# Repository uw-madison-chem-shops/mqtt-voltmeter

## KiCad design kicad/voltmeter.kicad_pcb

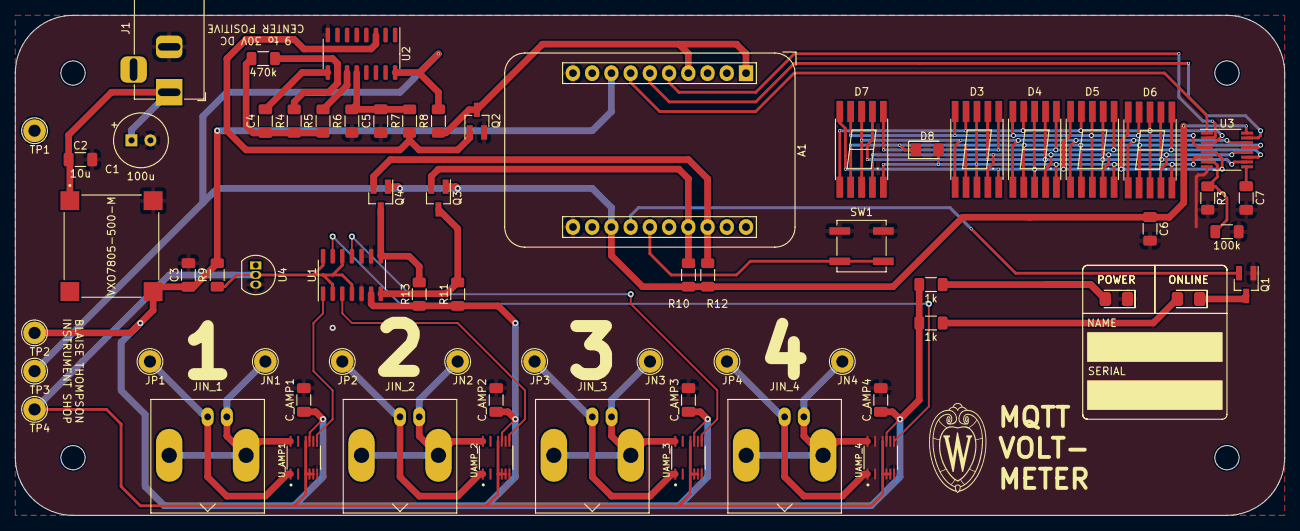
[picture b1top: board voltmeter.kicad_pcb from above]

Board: 2 copper layers, 167.6 x 66.0 mm, 68 parts (0 on the bottom side), 47 nets.

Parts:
A1: Adafruit_HUZZAH_ESP8266_breakout
C1: 100u; CP_Radial_Tantal_D7.0mm_P2.50mm
C2: 10u; C_1206_3216Metric_Pad1.33x1.80mm_HandSolder
C3: 22u; C_1206_3216Metric_Pad1.33x1.80mm_HandSolder
C4, C5: 1u; C_1206_3216Metric_Pad1.33x1.80mm_HandSolder
C6: 100n; C_1206_3216Metric_Pad1.33x1.80mm_HandSolder
C7: 20p; C_1206_3216Metric_Pad1.33x1.80mm_HandSolder
C_AMP1, C_AMP2, C_AMP3, C_AMP4: 100n; C_1206_3216Metric_Pad1.33x1.80mm_HandSolder
D1, D1#2, D2, D2#2, D8: LED; LED_1206_3216Metric_Pad1.42x1.75mm_HandSolder
D3, D4, D5, D6, D7: ACSC02-41SURKWA-F01
J1: Barrel_Jack; BarrelJack_Horizontal
JIN_1, JIN_2, JIN_3, JIN_4: IN-COAX; BNC_Amphenol_B6252HB-NPP3G-50_Horizontal
JN1, JN2, JN3, JN4: IN-; TestPoint_Loop_D2.60mm_Drill1.6mm_Beaded
JP1, JP2, JP3, JP4: IN+; TestPoint_Loop_D2.60mm_Drill1.6mm_Beaded
PS1: VXO7805-500-M; CONV_VXO7805-500-M
Q1, Q2, Q3, Q4: 2N7000; SOT-23_Handsoldering
R1, R2: 1k; R_1206_3216Metric_Pad1.30x1.75mm_HandSolder
R3, R3#2: 100k; R_1206_3216Metric_Pad1.30x1.75mm_HandSolder
R4, R4#2: 470k; R_1206_3216Metric_Pad1.30x1.75mm_HandSolder
R5, R6: 1M; R_1206_3216Metric_Pad1.30x1.75mm_HandSolder
R7, R8: 4.7k; R_1206_3216Metric_Pad1.30x1.75mm_HandSolder
R9: 470; R_1206_3216Metric_Pad1.30x1.75mm_HandSolder
R10, R11, R12, R13: 4K7; R_1206_3216Metric_Pad1.30x1.75mm_HandSolder
SW1: SW_Push; SW_SPST_B3SL-1022P
TP1, TP2, TP3, TP4: TestPoint; TestPoint_Loop_D2.60mm_Drill1.6mm_Beaded
U1: MCP3428; SOIC-14_3.9x8.7mm_P1.27mm
U2: CD4060BM96; SOIC-16_3.9x9.9mm_P1.27mm
U3: MAX6951; QSOP-16_3.9x4.9mm_P0.635mm
U4: LM285Z-2.5; TO-92_Inline
UAMP_2, UAMP_3, UAMP_4: LT1997HMS-3#PBF; SOP50P490X110-16N
U_AMP1: LT1997HMS-3#PBF; SOP50P490X110-16N

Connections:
+2V5: R9.2, TP4.1, U1.2 (CH1-), U1.4 (CH2-), U1.12 (CH3-), U1.14 (CH4-), U4.2 (K), UAMP_2.5 (+INC), UAMP_2.6 (REF1), UAMP_2.7 (REF2), UAMP_2.12 (-INC), UAMP_3.5 (+INC), UAMP_3.6 (REF1), UAMP_3.7 (REF2), UAMP_3.12 (-INC), UAMP_4.5 (+INC), UAMP_4.6 (REF1), UAMP_4.7 (REF2), UAMP_4.12 (-INC), U_AMP1.5 (+INC), U_AMP1.6 (REF1), U_AMP1.7 (REF2), U_AMP1.12 (-INC)
+3V3: A1.13 (3V), C6.1, Q3.1 (G), Q4.1 (G), R8.1, R10.1, R12.1, TP3.1, U2.16 (VDD), U3.16 (V+)
+5V: A1.8 (V+), C3.1, C_AMP1.1, C_AMP2.1, C_AMP3.1, C_AMP4.1, PS1.3 (+VO), R1.1, R2.1, R9.1, R11.1, R13.1, TP2.1, U1.6 (VDD), UAMP_2.11 (V+), UAMP_3.11 (V+), UAMP_4.11 (V+), U_AMP1.11 (V+)
/difference-amplifier1/V_OUT: U1.1 (CH1+), U_AMP1.9 (OUT)
/difference-amplifier2/V_OUT: U1.3 (CH2+), UAMP_2.9 (OUT)
/difference-amplifier3/V_OUT: U1.11 (CH3+), UAMP_3.9 (OUT)
/difference-amplifier4/V_OUT: U1.13 (CH4+), UAMP_4.9 (OUT)
/display/SEG0: D3.3 (C.K.), D3.8 (C.K.), D4.5 (DP), D5.5 (DP), D6.5 (DP), D7.5 (DP), D8.2 (A), U3.6 (DIG0/SEG0)
/display/SEG1: D3.5 (DP), D4.3 (C.K.), D4.8 (C.K.), D5.10 (g), D6.10 (g), D7.10 (g), U3.5 (DIG1/SEG1)
/display/SEG2: D3.10 (g), D4.10 (g), D5.3 (C.K.), D5.8 (C.K.), D6.9 (f), D7.9 (f), U3.4 (DIG2/SEG2)
/display/SEG3: D3.9 (f), D4.9 (f), D5.9 (f), D6.3 (C.K.), D6.8 (C.K.), D7.1 (e), U3.3 (DIG3/SEG3)
/display/SEG4: D3.1 (e), D4.1 (e), D5.1 (e), D6.1 (e), D7.3 (C.K.), D7.8 (C.K.), U3.14 (DIG4/SEG4)
/display/SEG5: D3.2 (d), D4.2 (d), D5.2 (d), D6.2 (d), D7.2 (d), D8.1 (K), U3.13 (DIG5/SEG5)
/display/SEG6: D3.4 (c), D4.4 (c), D5.4 (c), D6.4 (c), D7.4 (c), U3.12 (DIG6/SEG6)
/display/SEG7: D3.6 (b), D4.6 (b), D5.6 (b), D6.6 (b), D7.6 (b), U3.11 (DIG7/SEG7)
/display/SEG8: D3.7 (a), D4.7 (a), D5.7 (a), D6.7 (a), D7.7 (a), U3.10 (SEG8)
/i2c-levelshift/SCL_HV: Q4.3 (D), R13.2, U1.8 (SCL)
/i2c-levelshift/SDA_HV: Q3.3 (D), R11.2, U1.7 (SDA)
DISPLAY_CS: A1.6 (12), U3.15 (~CS)
GND: A1.10 (GND), A1.11 (GND), C1.2, C2.2, C3.2, C5.2, C6.2, C7.2, C_AMP1.2, C_AMP2.2, C_AMP3.2, C_AMP4.2, D1.1 (K), D1#2.1 (K), J1.2, PS1.2 (GND), Q1.1 (S), Q2.2 (S), R3.2, R3#2.2, R6.2, SW1.1, TP1.1, U1.5 (VSS), U1.9 (Adr0), U1.10 (Adr1), U2.8 (GND), U3.8 (GND), U4.3 (A), UAMP_2.8 (V-), UAMP_3.8 (V-), UAMP_4.8 (V-), U_AMP1.8 (V-)
MOSI: A1.7 (13), U3.1 (DIN)
unnamed: A1.15 (2), SW1.2
unnamed: A1.14 (15), Q1.2 (G)
unnamed: C4.2, R4.1, R4#2.1, R5.1
unnamed: D1.2 (A), D1#2.2 (A), R1.2
unnamed: D2.2 (A), D2#2.2 (A), R2.2
unnamed: D2.1 (K), D2#2.1 (K), Q1.3 (D)
unnamed: JIN_1.2 (Ext), JN1.1, U_AMP1.16 (-INA)
unnamed: JIN_1.1 (In), JP1.1, U_AMP1.1 (+INA)
unnamed: JIN_2.2 (Ext), JN2.1, UAMP_2.16 (-INA)
unnamed: JIN_2.1 (In), JP2.1, UAMP_2.1 (+INA)
unnamed: JIN_3.2 (Ext), JN3.1, UAMP_3.16 (-INA)
unnamed: JIN_3.1 (In), JP3.1, UAMP_3.1 (+INA)
unnamed: JIN_4.2 (Ext), JN4.1, UAMP_4.16 (-INA)
unnamed: JIN_4.1 (In), JP4.1, UAMP_4.1 (+INA)
unnamed: C1.1, C2.1, J1.1, PS1.1 (+VIN)
unnamed: Q2.1 (G), R7.1, U2.3 (Q14)
unnamed: R4.2, R4#2.2, U2.10 (CLK_0)
unnamed: C4.1, U2.9 (CLK_0-1)
unnamed: R5.2, U2.11 (CLK_1)
unnamed: C5.1, R6.1, R7.2, U2.12 (RST)
unnamed: R3.1, R3#2.1, U3.7 (ISET)
unnamed: C7.1, U3.9 (OSC)
RST: A1.1 (~RST), A1.4 (16), Q2.3 (D), R8.2
SCK: A1.5 (14), U3.2 (CLK)
SCL: A1.18 (5), Q4.2 (S), R12.2
SDA: A1.17 (4), Q3.2 (S), R10.2

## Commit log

2021-01-26 copy paste
2023-11-21 reorg
2023-11-22 schematic
2023-11-27 passes drc
2024-03-05 firmware update
